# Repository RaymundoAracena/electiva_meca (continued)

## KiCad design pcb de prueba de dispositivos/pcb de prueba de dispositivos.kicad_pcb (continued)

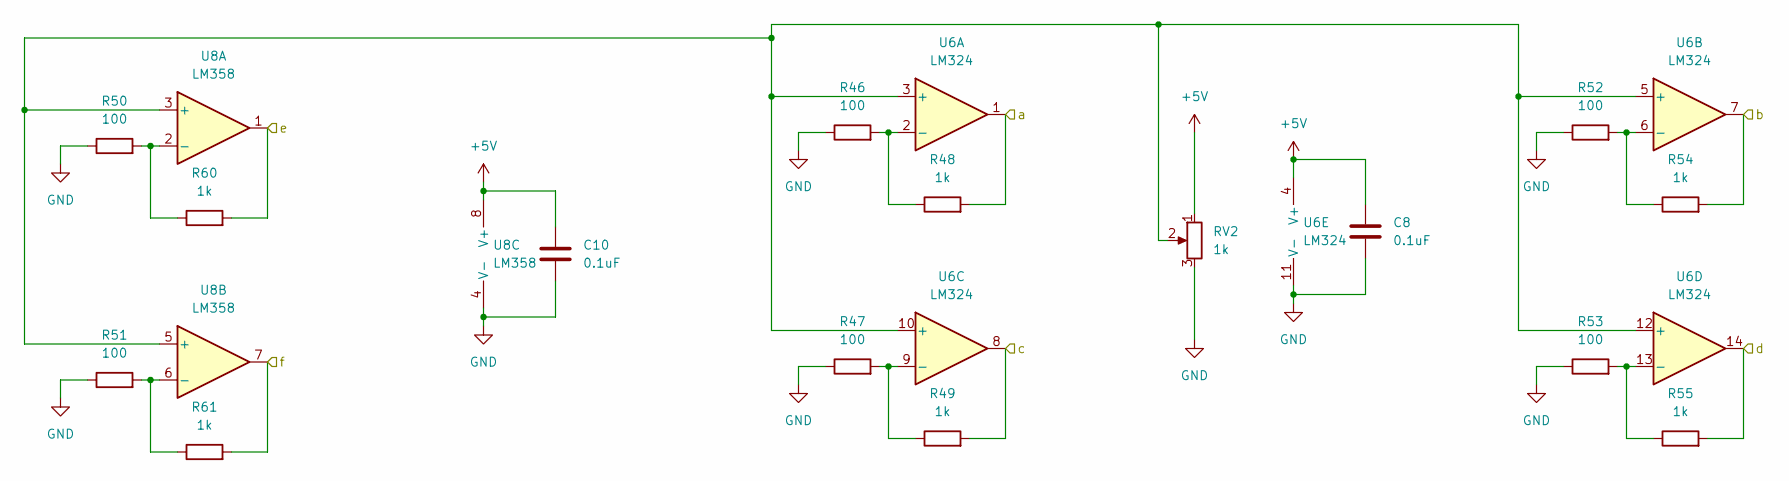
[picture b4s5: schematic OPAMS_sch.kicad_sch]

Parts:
C8, C10: 0.1uF; C_Disc_D5.0mm_W2.5mm_P5.00mm
R46, R47, R50, R51, R52, R53: 100; R_Axial_DIN0207_L6.3mm_D2.5mm_P10.16mm_Horizontal
R48, R49, R54, R55, R60, R61: 1k; R_Axial_DIN0207_L6.3mm_D2.5mm_P10.16mm_Horizontal
RV2: 1k; TerminalBlock_bornier-3_P5.08mm
U6: LM324; DIP-14_W7.62mm_LongPads
U8: LM358; DIP-8_W7.62mm_LongPads

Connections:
+5V: C8.2, C10.2, RV2.1, U6.4 (V+), U8.8 (V+); also elsewhere on the board
/OPAMS Y REGULADO/a: R48.2, U6.1; also elsewhere on the board
/OPAMS Y REGULADO/b: R54.2, U6.7; also elsewhere on the board
/OPAMS Y REGULADO/c: R49.2, U6.8; also elsewhere on the board
/OPAMS Y REGULADO/d: R55.2, U6.14; also elsewhere on the board
/OPAMS Y REGULADO/e: R60.2, U8.1; also elsewhere on the board
/OPAMS Y REGULADO/f: R61.2, U8.7; also elsewhere on the board
GND: C8.1, C10.1, R46.1, R47.1, R50.1, R51.1, R52.1, R53.1, RV2.3, U6.11 (V-), U8.4 (V-); also elsewhere on the board
unnamed: R46.2, R48.1, U6.2 (-)
unnamed: R47.2, R49.1, U6.9 (-)
unnamed: R50.2, R60.1, U8.2 (-)
unnamed: R51.2, R61.1, U8.6 (-)
unnamed: R52.2, R54.1, U6.6 (-)
unnamed: R53.2, R55.1, U6.13 (-)
unnamed: RV2.2, U6.3 (+), U6.5 (+), U6.10 (+), U6.12 (+), U8.3 (+), U8.5 (+)

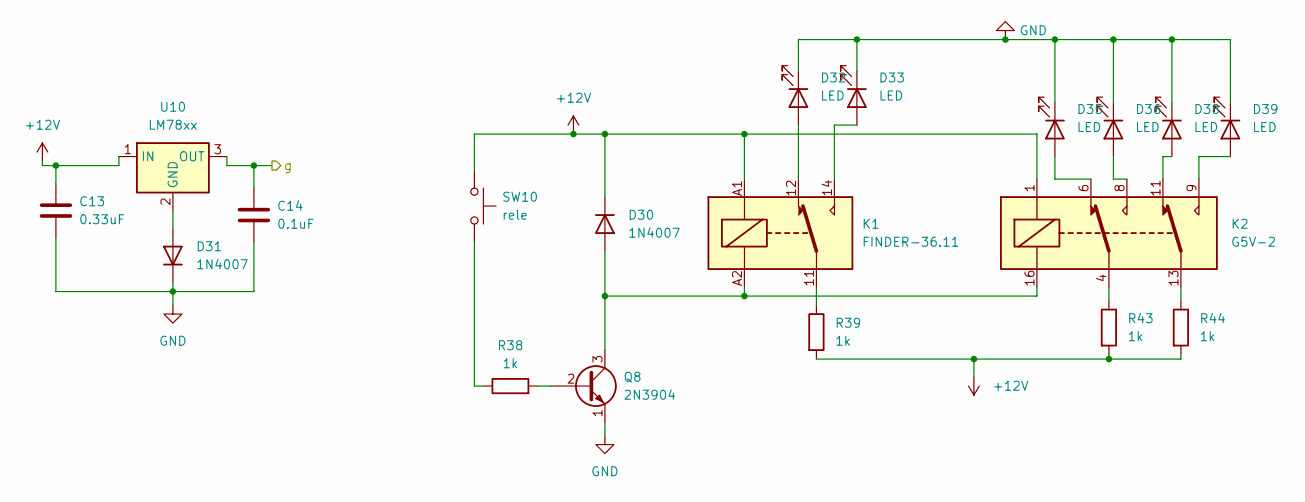
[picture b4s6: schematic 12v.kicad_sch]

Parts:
C13: 0.33uF; C_Disc_D5.0mm_W2.5mm_P5.00mm
C14: 0.1uF; C_Disc_D5.0mm_W2.5mm_P5.00mm
D30, D31: 1N4007; D_DO-41_SOD81_P10.16mm_Horizontal
D32, D33, D35, D36, D38, D39: LED; LED_D5.0mm
K1: FINDER-36.11; Relay_SPDT_Finder_36.11
K2: G5V-2; Relay_DPDT_Omron_G5V-2
Q8: 2N3904; TO-92_Wide
R38, R39, R43, R44: 1k; R_Axial_DIN0207_L6.3mm_D2.5mm_P10.16mm_Horizontal
SW10: rele; SW_PUSH_6mm
U10: LM78xx; TO-220-3_Vertical

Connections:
+12V: C13.1, D30.1 (K), K1.A1, K2.1, R39.2, R43.2, R44.2, SW10.1, U10.1 (IN); also elsewhere on the board
/12v/g: C14.1, U10.3 (OUT); also elsewhere on the board
GND: C13.2, C14.2, D31.1 (K), D32.1 (K), D33.1 (K), D35.1 (K), D36.1 (K), D38.1 (K), D39.1 (K), Q8.1 (E); also elsewhere on the board
unnamed: D30.2 (A), K1.A2, K2.16, Q8.3 (C)
unnamed: D31.2 (A), U10.2 (GND)
unnamed: D32.2 (A), K1.12
unnamed: D33.2 (A), K1.14
unnamed: D35.2 (A), K2.6
unnamed: D36.2 (A), K2.8
unnamed: D38.2 (A), K2.11
unnamed: D39.2 (A), K2.9
unnamed: K1.11, R39.1
unnamed: K2.4, R43.1
unnamed: K2.13, R44.1
unnamed: Q8.2 (B), R38.2
unnamed: R38.1, SW10.2

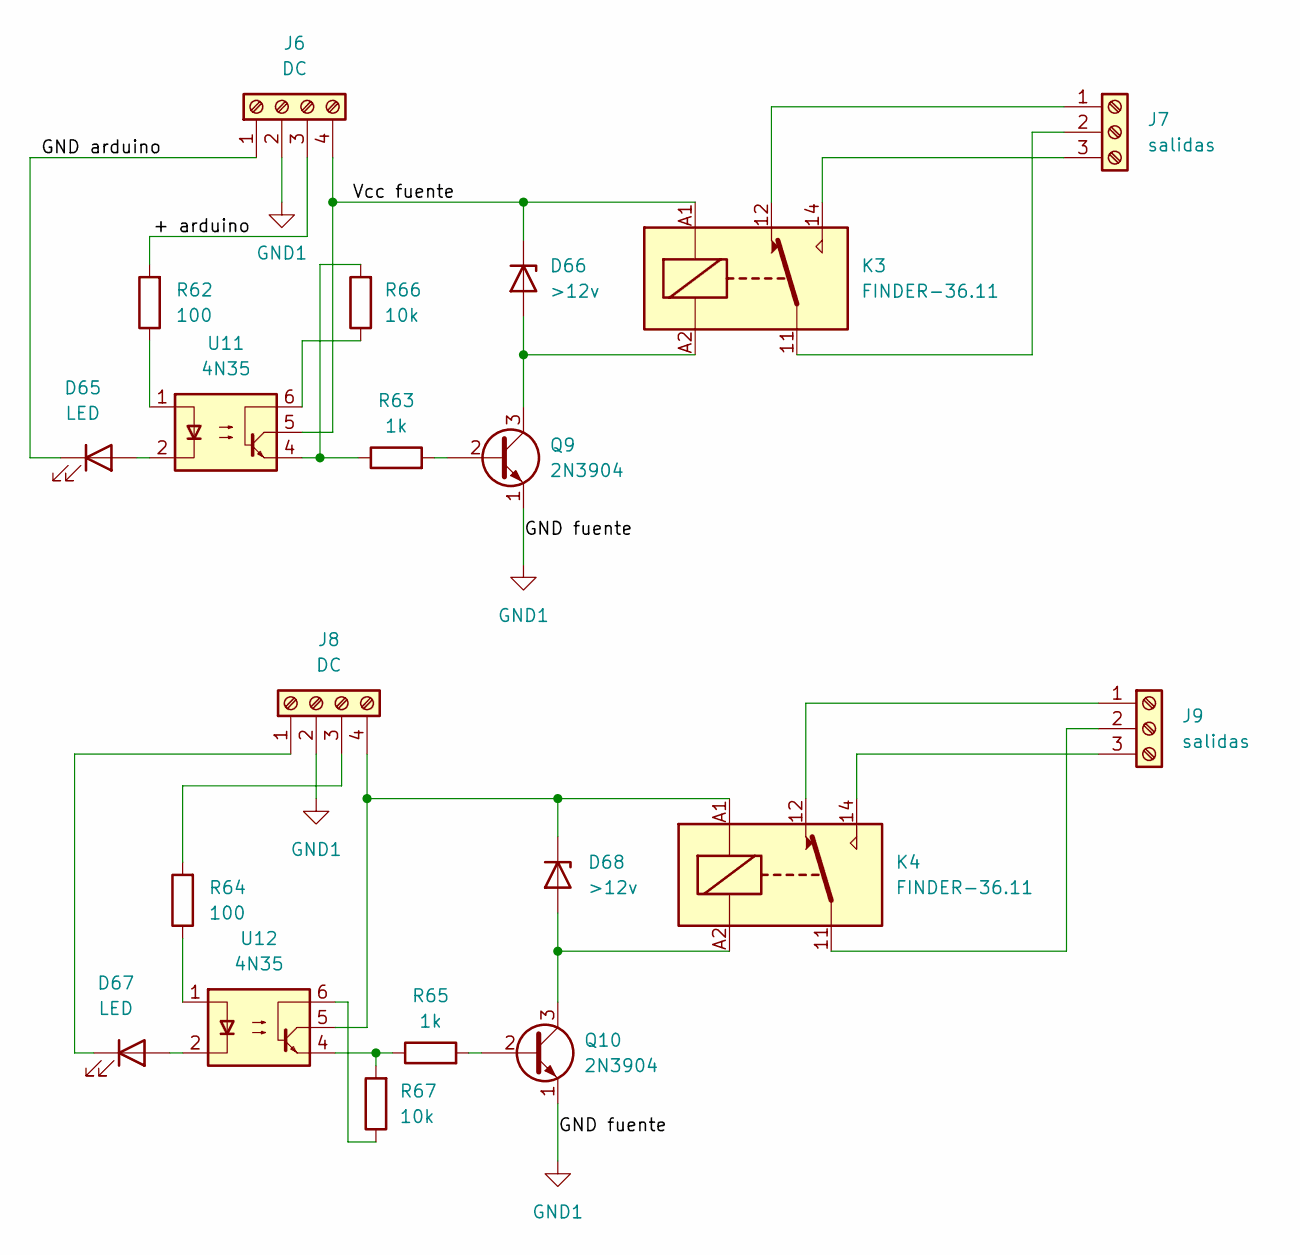
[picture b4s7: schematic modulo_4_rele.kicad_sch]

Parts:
D65, D67: LED; LED_D5.0mm
D66, D68: >12v; D_A-405_P10.16mm_Horizontal
J6, J8: DC; PinHeader_1x04_P2.54mm_Vertical
J7, J9: salidas; TerminalBlock_bornier-3_P5.08mm
K3, K4: FINDER-36.11; Relay_SPDT_Finder_36.11
Q9, Q10: 2N3904; TO-92_Wide
R62, R64: 100; R_Axial_DIN0207_L6.3mm_D2.5mm_P10.16mm_Horizontal
R63, R65: 1k; R_Axial_DIN0207_L6.3mm_D2.5mm_P10.16mm_Horizontal
R66, R67: 10k; R_Axial_DIN0207_L6.3mm_D2.5mm_P10.16mm_Horizontal
U11, U12: 4N35; DIP-6_W7.62mm

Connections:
/modulo_4_rele/+ arduino: J6.3, R62.2
/modulo_4_rele/GND arduino: D65.1 (K), J6.1
/modulo_4_rele/Vcc fuente: D66.1 (K), J6.4, K3.A1, U11.5
GND1: J6.2, J8.2, Q9.1 (E), Q10.1 (E)
unnamed: D65.2 (A), U11.2
unnamed: D66.2 (A), K3.A2, Q9.3 (C)
unnamed: D67.1 (K), J8.1
unnamed: D67.2 (A), U12.2
unnamed: D68.1 (K), J8.4, K4.A1, U12.5
unnamed: D68.2 (A), K4.A2, Q10.3 (C)
unnamed: J7.1, K3.12
unnamed: J7.2, K3.11
unnamed: J7.3, K3.14
unnamed: J8.3, R64.2
unnamed: J9.1, K4.12
unnamed: J9.2, K4.11
unnamed: J9.3, K4.14
unnamed: Q9.2 (B), R63.2
unnamed: Q10.2 (B), R65.2
unnamed: R62.1, U11.1
unnamed: R63.1, R66.2, U11.4
unnamed: R64.1, U12.1
unnamed: R65.1, R67.2, U12.4
unnamed: R66.1, U11.6
unnamed: R67.1, U12.6

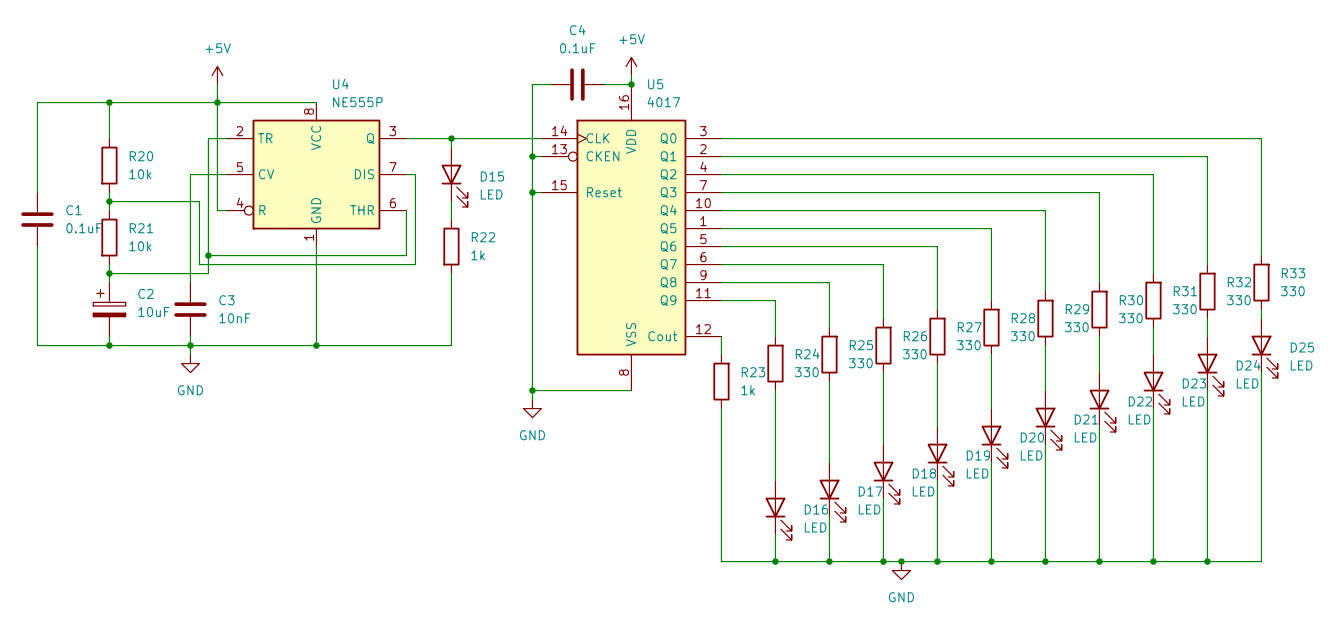
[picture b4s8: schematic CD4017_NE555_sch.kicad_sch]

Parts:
C1, C4: 0.1uF; C_Disc_D5.0mm_W2.5mm_P5.00mm
C2: 10uF; CP_Radial_D5.0mm_P2.50mm
C3: 10nF; C_Disc_D5.0mm_W2.5mm_P5.00mm
D15, D16, D17, D18, D19, D20, D21, D22, D23, D24, D25: LED; LED_D5.0mm
R20, R21: 10k; R_Axial_DIN0207_L6.3mm_D2.5mm_P10.16mm_Horizontal
R22, R23: 1k; R_Axial_DIN0207_L6.3mm_D2.5mm_P10.16mm_Horizontal
R24, R25, R26, R27, R28, R29, R30, R31, R32, R33: 330; R_Axial_DIN0207_L6.3mm_D2.5mm_P10.16mm_Horizontal
U4: NE555P; DIP-8_W7.62mm
U5: 4017; DIP-16_W7.62mm_LongPads

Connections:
+5V: C1.2, C4.1, R20.1, U4.4 (R), U4.8 (VCC), U5.16 (VDD); also elsewhere on the board
GND: C1.1, C2.2, C3.2, C4.2, D16.1 (K), D17.1 (K), D18.1 (K), D19.1 (K), D20.1 (K), D21.1 (K), D22.1 (K), D23.1 (K), D24.1 (K), D25.1 (K), R22.2, R23.1, U4.1 (GND), U5.8 (VSS), U5.13 (CKEN), U5.15 (Reset); also elsewhere on the board
unnamed: C2.1, R21.2, U4.2 (TR), U4.6 (THR)
unnamed: C3.1, U4.5 (CV)
unnamed: D15.1 (K), R22.1
unnamed: D15.2 (A), U4.3 (Q), U5.14 (CLK)
unnamed: D16.2 (A), R24.1
unnamed: D17.2 (A), R25.1
unnamed: D18.2 (A), R26.1
unnamed: D19.2 (A), R27.1
unnamed: D20.2 (A), R28.1
unnamed: D21.2 (A), R29.1
unnamed: D22.2 (A), R30.1
unnamed: D23.2 (A), R31.1
unnamed: D24.2 (A), R32.1
unnamed: D25.2 (A), R33.1
unnamed: R20.2, R21.1, U4.7 (DIS)
unnamed: R23.2, U5.12 (Cout)
unnamed: R24.2, U5.11 (Q9)
unnamed: R25.2, U5.9 (Q8)
unnamed: R26.2, U5.6 (Q7)
unnamed: R27.2, U5.5 (Q6)
unnamed: R28.2, U5.1 (Q5)
unnamed: R29.2, U5.10 (Q4)
unnamed: R30.2, U5.7 (Q3)
unnamed: R31.2, U5.4 (Q2)
unnamed: R32.2, U5.2 (Q1)
unnamed: R33.2, U5.3 (Q0)

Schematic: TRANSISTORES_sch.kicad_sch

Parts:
D26, D28, D34, D37: LED; LED_D5.0mm
D27: SCR; TO-225
Q1: 2N3904; TO-92_Wide
Q2: BD137; TO-126-3_Vertical
Q3: TIP122; TO-220-3_Vertical
Q4: 2N3906; TO-92_Wide
Q5: BD136; TO-126-3_Vertical
Q6: TIP125; TO-220-3_Vertical
R34, R35, R40, R41: 1k; R_Axial_DIN0207_L6.3mm_D2.5mm_P10.16mm_Horizontal
R36, R37, R42, R45: 330; R_Axial_DIN0207_L6.3mm_D2.5mm_P10.16mm_Horizontal
R56: 10k; R_Axial_DIN0207_L6.3mm_D2.5mm_P10.16mm_Horizontal
SW6: ON; SW_PUSH_6mm
SW7, SW9: sw; SW_PUSH_6mm
SW8: OFF; SW_PUSH_6mm

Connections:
+5V: D26.2 (A), D28.2 (A), D34.2 (A), D37.2 (A), SW6.2, SW7.2, SW9.2; also elsewhere on the board
GND: D27.3 (K), Q1.1 (E), Q2.1 (E), Q3.3 (E), Q4.3 (C), Q5.2 (C), Q6.2 (C), R40.1, R45.1, R56.1, SW8.2; also elsewhere on the board
unnamed: D26.1 (K), R36.2
unnamed: D27.1 (G), R35.2, R56.2
unnamed: D27.2 (A), R36.1, SW8.1
unnamed: D28.1 (K), R37.2
unnamed: D34.1 (K), R42.2
unnamed: D37.1 (K), R45.2
unnamed: Q1.2 (B), Q2.3 (B), Q3.1 (B), R34.2
unnamed: Q1.3 (C), Q2.2 (C), Q3.2 (C), R37.1
unnamed: Q4.1 (E), Q5.1 (E), Q6.3 (E), R42.1
unnamed: Q4.2 (B), Q5.3 (B), Q6.1 (B), R41.2
unnamed: R34.1, SW7.1
unnamed: R35.1, SW6.1
unnamed: R40.2, R41.1, SW9.1

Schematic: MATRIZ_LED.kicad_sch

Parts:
D40, D41, D42, D43, D44, D45, D46, D47, D48, D49, D50, D51, D52, D53, D54, D55, D56, D57, D58, D59, D60, D61, D62, D63, D64: LED; LED_D5.0mm
J3: + matriz led; PinSocket_1x05_P2.54mm_Vertical
J4: GND matriz; PinSocket_1x05_P2.54mm_Vertical

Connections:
unnamed: D40.1 (K), D45.1 (K), D50.1 (K), D55.1 (K), D60.1 (K), J4.1
unnamed: D40.2 (A), D41.2 (A), D42.2 (A), D43.2 (A), D44.2 (A), J3.1
unnamed: D41.1 (K), D46.1 (K), D51.1 (K), D56.1 (K), D61.1 (K), J4.2
unnamed: D42.1 (K), D47.1 (K), D52.1 (K), D57.1 (K), D62.1 (K), J4.3
unnamed: D43.1 (K), D48.1 (K), D53.1 (K), D58.1 (K), D63.1 (K), J4.4
unnamed: D44.1 (K), D49.1 (K), D54.1 (K), D59.1 (K), D64.1 (K), J4.5
unnamed: D45.2 (A), D46.2 (A), D47.2 (A), D48.2 (A), D49.2 (A), J3.2
unnamed: D50.2 (A), D51.2 (A), D52.2 (A), D53.2 (A), D54.2 (A), J3.3
unnamed: D55.2 (A), D56.2 (A), D57.2 (A), D58.2 (A), D59.2 (A), J3.4
unnamed: D60.2 (A), D61.2 (A), D62.2 (A), D63.2 (A), D64.2 (A), J3.5

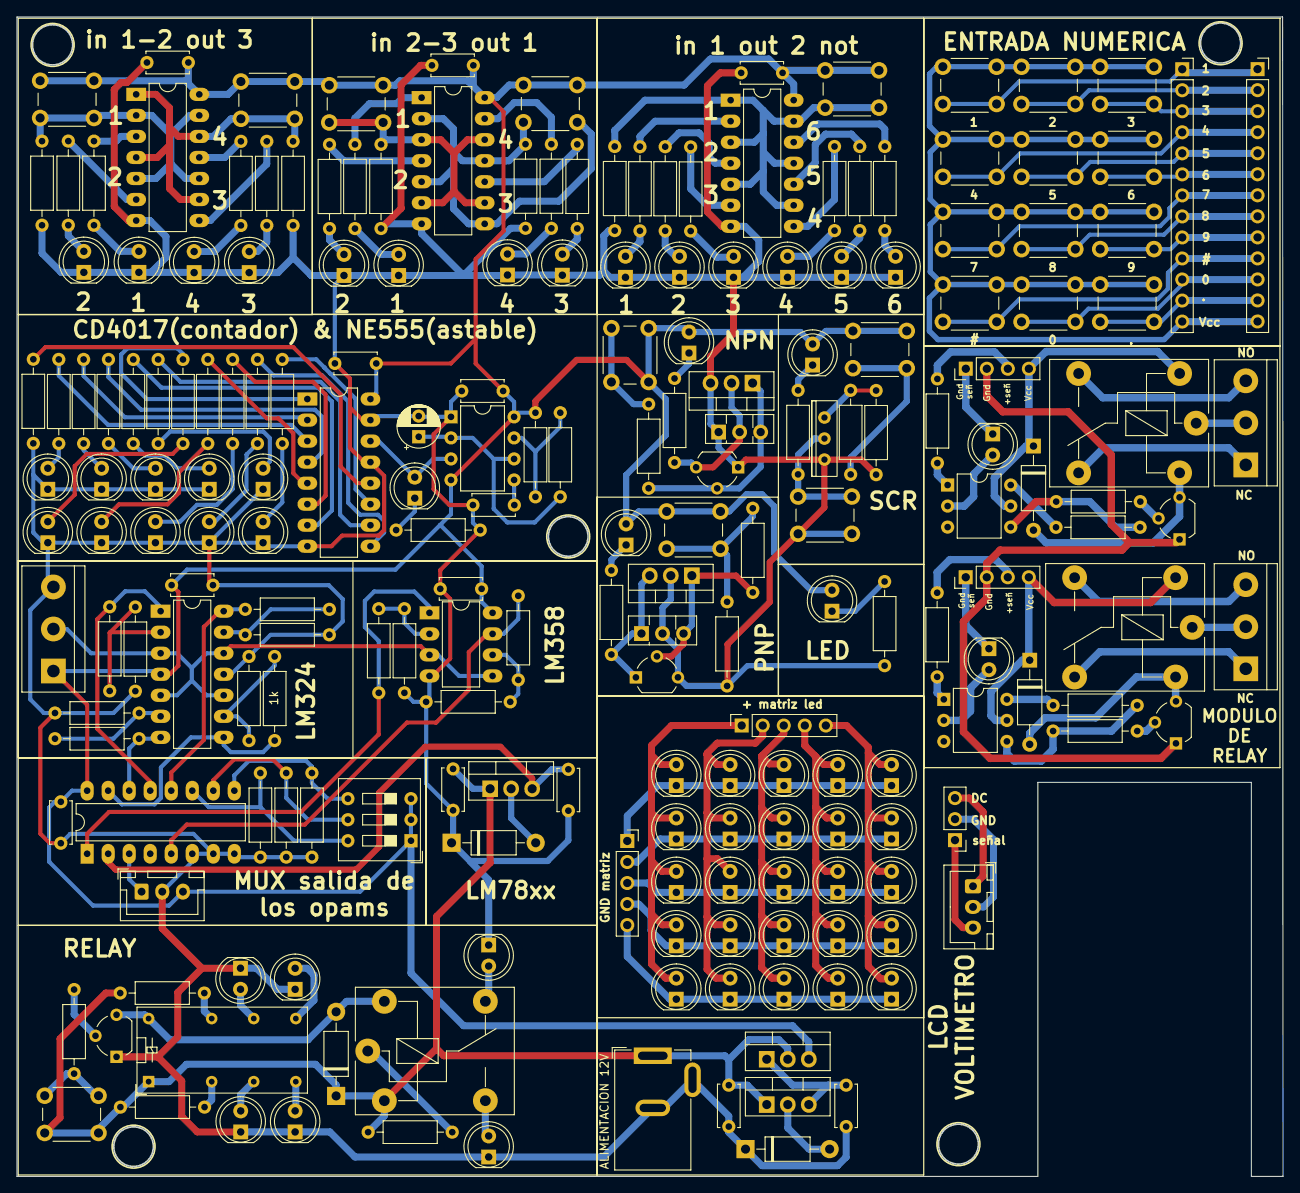
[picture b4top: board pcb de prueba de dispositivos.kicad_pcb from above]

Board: 2 copper layers, 152.9 x 140.1 mm, 211 parts (0 on the bottom side), 159 nets.

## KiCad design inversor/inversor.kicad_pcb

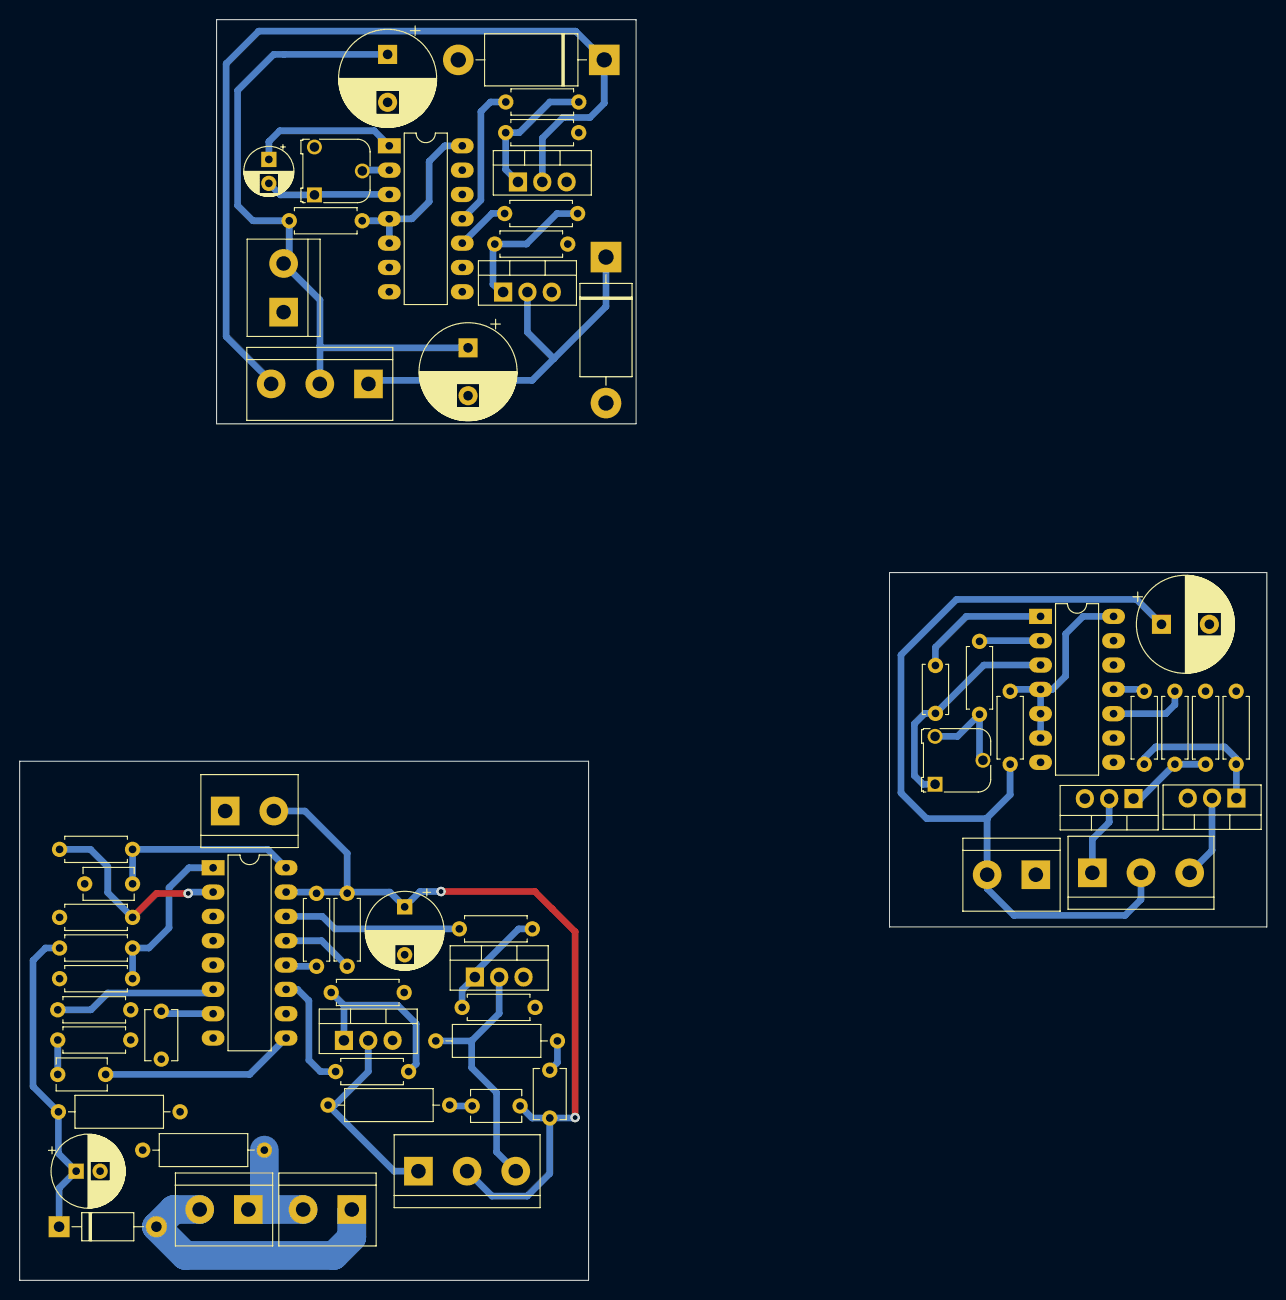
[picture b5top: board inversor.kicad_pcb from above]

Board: 2 copper layers, 130.2 x 131.6 mm, 61 parts (0 on the bottom side), 47 nets.

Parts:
C1: 10nF; C_Disc_D5.0mm_W2.5mm_P5.00mm
C2, C10, C12: 1000uF; CP_Radial_D10.0mm_P5.00mm
C3: 100uF; CP_Radial_D8.0mm_P5.00mm
C4, C5: 0.1uF; C_Disc_D5.1mm_W3.2mm_P5.00mm
C6: 0.001uF; C_Disc_D5.1mm_W3.2mm_P5.00mm
C7, C8: 100nF; C_Disc_D5.1mm_W3.2mm_P5.00mm
C9: 1uF; CP_Radial_D7.5mm_P2.50mm
C11: 4.7uF; CP_Radial_D5.0mm_P2.50mm
D1: 1N4007; D_DO-41_SOD81_P10.16mm_Horizontal
D2, D3: 1N5408; D_DO-201AD_P15.24mm_Horizontal
J1: Screw_Terminal_01x03; TerminalBlock_bornier-3_P5.08mm
J2, J6, J7: DC; TerminalBlock_bornier-2_P5.08mm
J3: 12-12; TerminalBlock_bornier-3_P5.08mm
J4: 120; TerminalBlock_bornier-2_P5.08mm
J5: 120ref; TerminalBlock_bornier-2_P5.08mm
J8: AC; TerminalBlock_bornier-3_P5.08mm
Q1, Q2, Q3, Q4, Q5, Q6: IRF3205; TO-220-3_Vertical
R1, R15: 330; R_Axial_DIN0207_L6.3mm_D2.5mm_P7.62mm_Horizontal
R2: 390k; R_Axial_DIN0207_L6.3mm_D2.5mm_P7.62mm_Horizontal
R3, R4: 220; R_Axial_DIN0207_L6.3mm_D2.5mm_P7.62mm_Horizontal
R5, R6, R16, R22: 2200; R_Axial_DIN0207_L6.3mm_D2.5mm_P7.62mm_Horizontal
R7, R8, R19, R21: 1k; R_Axial_DIN0207_L6.3mm_D2.5mm_P7.62mm_Horizontal
R9, R13: 100k; R_Axial_DIN0207_L6.3mm_D2.5mm_P7.62mm_Horizontal
R10, R11: 47k; R_Axial_DIN0207_L6.3mm_D2.5mm_P7.62mm_Horizontal
R12, R27, R28: 10k; R_Axial_DIN0207_L6.3mm_D2.5mm_P7.62mm_Horizontal
R14: 20k; R_Axial_DIN0207_L6.3mm_D2.5mm_P7.62mm_Horizontal
R18, R20: 22; R_Axial_DIN0207_L6.3mm_D2.5mm_P7.62mm_Horizontal
R23: 56/2W; R_Axial_DIN0309_L9.0mm_D3.2mm_P12.70mm_Horizontal
R24: 66/2W; R_Axial_DIN0309_L9.0mm_D3.2mm_P12.70mm_Horizontal
R25: 200k/2W; R_Axial_DIN0309_L9.0mm_D3.2mm_P12.70mm_Horizontal
R26: 1k/1W; R_Axial_DIN0309_L9.0mm_D3.2mm_P12.70mm_Horizontal
RV1, RV2: 100k; Potentiometer_Runtron_RM-065_Vertical
U1, U3: 4047; DIP-14_W7.62mm_LongPads
U2: SG3525; DIP-16_W7.62mm_LongPads

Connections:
+12P: C10.1, C12.1, J7.2, J8.2, R15.1
+12V: C3.1, C7.1, C8.2, J3.2, J6.2, R7.1, R8.2, U2.15 (VIN)
+12VA: C2.1, J1.2, J2.2, R1.1
GND: C3.2, C4.1, C5.1, C9.2, J6.1, Q3.3 (S), Q6.3 (S), R9.1, R11.1, R12.1, R14.1, R16.2, R22.2, R25.1, R26.2, U2.4 (OSC), U2.5 (CT), U2.8 (SS)
GND1: C2.2, J2.1, Q1.3 (S), Q2.3 (S), R5.1, R6.1, U1.7 (VSS), U1.8 (+TRIGGER), U1.9 (EXT_RESET), U1.12 (RETRIGGER)
GNDA: C10.2, C12.2, D2.2 (A), D3.2 (A), J7.1, Q4.3 (S), Q5.3 (S), R27.1, R28.1, U3.6 (-TRIGGER), U3.7 (VSS), U3.8 (+TRIGGER), U3.9 (EXT_RESET), U3.12 (RETRIGGER)
unnamed: C6.1, R14.2
unnamed: C7.2, R23.2
unnamed: C8.1, R24.1
unnamed: D1.2 (A), J4.2, J5.1
unnamed: D2.1 (K), J8.1, Q4.2 (D)
unnamed: D3.1 (K), J8.3, Q5.2 (D)
unnamed: J1.1, Q1.2 (D)
unnamed: J1.3, Q2.2 (D)
unnamed: J3.1, Q3.2 (D), R23.1
unnamed: J3.3, Q6.2 (D), R24.2
unnamed: J4.1, J5.2, R25.2
unnamed: Q1.1 (G), R3.2, R5.2
unnamed: Q2.1 (G), R4.2, R6.2
unnamed: Q3.1 (G), R16.1, R18.2
unnamed: Q4.1 (G), R19.2, R27.2
unnamed: Q5.1 (G), R21.2, R28.2
unnamed: Q6.1 (G), R20.2, R22.1
unnamed: R2.1, RV1.2, RV1.3
unnamed: R1.2, U1.4 (~ASTABLE), U1.5 (ASTABLE), U1.6 (-TRIGGER), U1.14 (VDD)
unnamed: C1.2, U1.1 (C)
unnamed: R3.1, U1.10 (Q)
unnamed: R2.2, U1.2 (R)
unnamed: C1.1, RV1.1, U1.3 (RC_COMMON)
unnamed: R4.1, U1.11 (~Q)
unnamed: C6.2, U2.9 (COMP)
unnamed: C4.2, U2.7 (DISCH)
unnamed: R8.1, U2.12 (GND)
unnamed: R12.2, R13.1, U2.1 (INV)
unnamed: R10.2, R11.2, U2.2 (NI)
unnamed: R18.1, U2.11 (OUTA)
unnamed: R20.1, U2.14 (OUTB)
unnamed: C5.2, R10.1, U2.16 (REF)
unnamed: R9.2, U2.6 (RT)
unnamed: R7.2, U2.13 (VC)
unnamed: R15.2, U3.4 (~ASTABLE), U3.5 (ASTABLE), U3.14 (VDD)
unnamed: C11.1, U3.1 (C)
unnamed: R19.1, U3.10 (Q)
unnamed: RV2.2, U3.2 (R)
unnamed: C11.2, RV2.1, U3.3 (RC_COMMON)
unnamed: R21.1, U3.11 (~Q)
pb1: C9.1, D1.1 (K), R13.2, R26.1

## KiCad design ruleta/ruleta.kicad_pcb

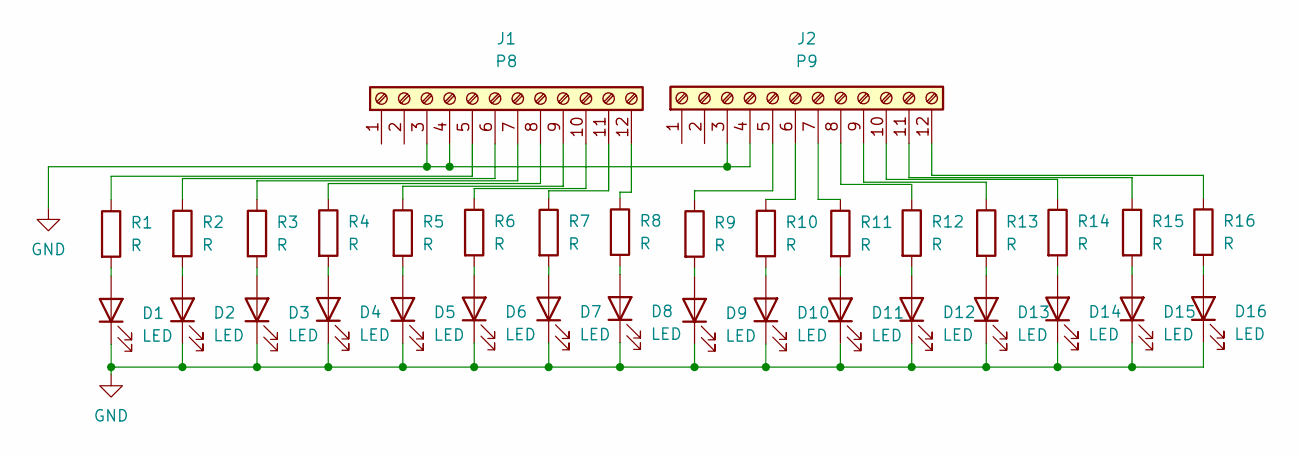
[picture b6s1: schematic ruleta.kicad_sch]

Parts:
D1, D2, D3, D4, D5, D6, D7, D8, D9, D10, D11, D12, D13, D14, D15, D16: LED; LED_D5.0mm
J1: P8; PinHeader_2x06_P2.54mm_Horizontal
J2: P9; PinHeader_2x06_P2.54mm_Horizontal
R1, R2, R3, R4, R5, R6, R7, R8, R9, R10, R11, R12, R13, R14, R15, R16: R; R_Axial_DIN0207_L6.3mm_D2.5mm_P10.16mm_Horizontal

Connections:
GND: D1.1 (K), D2.1 (K), D3.1 (K), D4.1 (K), D5.1 (K), D6.1 (K), D7.1 (K), D8.1 (K), D9.1 (K), D10.1 (K), D11.1 (K), D12.1 (K), D13.1 (K), D14.1 (K), D15.1 (K), D16.1 (K), J1.3, J1.4, J2.3, J2.4
unnamed: D1.2 (A), R1.2
unnamed: D2.2 (A), R2.2
unnamed: D3.2 (A), R3.2
unnamed: D4.2 (A), R4.2
unnamed: D5.2 (A), R5.2
unnamed: D6.2 (A), R6.2
unnamed: D7.2 (A), R7.2
unnamed: D8.2 (A), R8.2
unnamed: D9.2 (A), R9.2
unnamed: D10.2 (A), R10.2
unnamed: D11.2 (A), R11.2
unnamed: D12.2 (A), R12.2
unnamed: D13.2 (A), R13.2
unnamed: D14.2 (A), R14.2
unnamed: D15.2 (A), R15.2
unnamed: D16.2 (A), R16.2
unnamed: J1.5, R1.1
unnamed: J1.6, R2.1
unnamed: J1.7, R3.1
unnamed: J1.8, R4.1
unnamed: J1.9, R5.1
unnamed: J1.10, R6.1
unnamed: J1.11, R7.1
unnamed: J1.12, R8.1
unnamed: J2.5, R9.1
unnamed: J2.6, R10.1
unnamed: J2.7, R11.1
unnamed: J2.8, R12.1
unnamed: J2.9, R13.1
unnamed: J2.10, R14.1
unnamed: J2.11, R15.1
unnamed: J2.12, R16.1

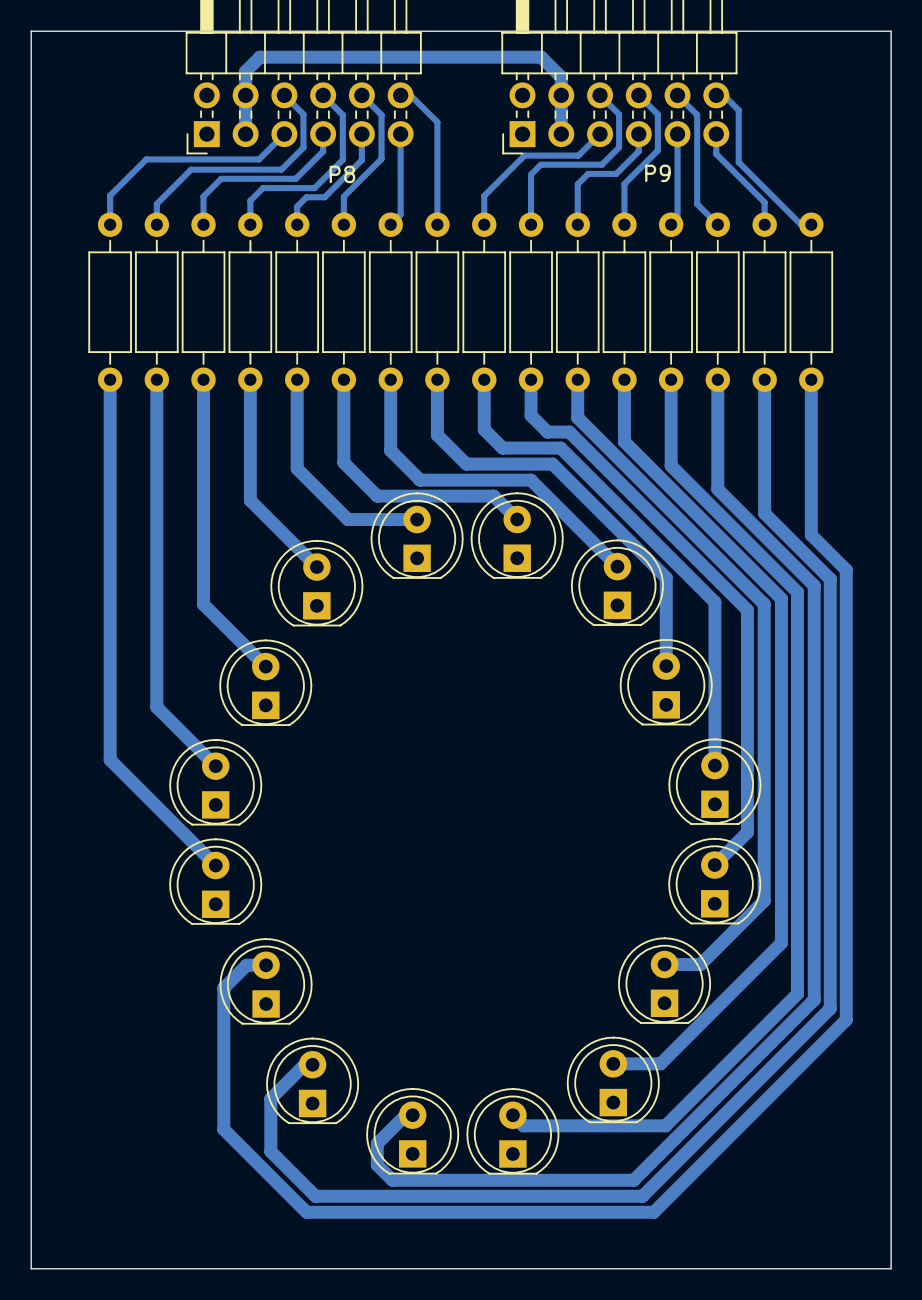
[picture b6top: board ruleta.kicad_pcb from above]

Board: 2 copper layers, 56.4 x 81.1 mm, 34 parts (0 on the bottom side), 33 nets.

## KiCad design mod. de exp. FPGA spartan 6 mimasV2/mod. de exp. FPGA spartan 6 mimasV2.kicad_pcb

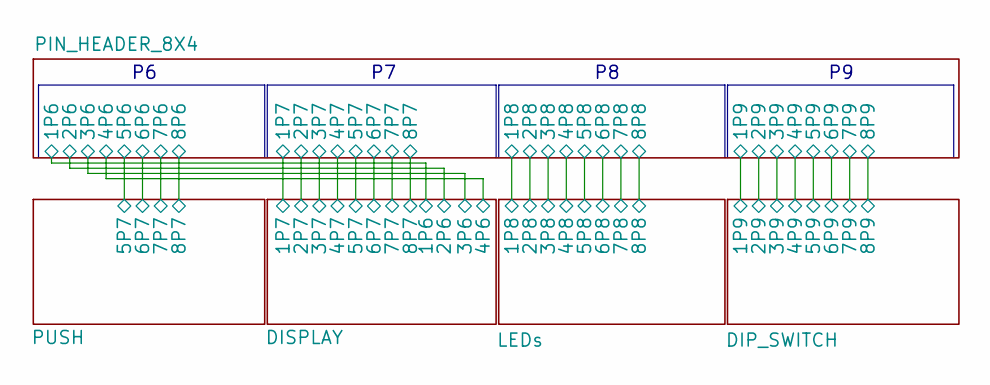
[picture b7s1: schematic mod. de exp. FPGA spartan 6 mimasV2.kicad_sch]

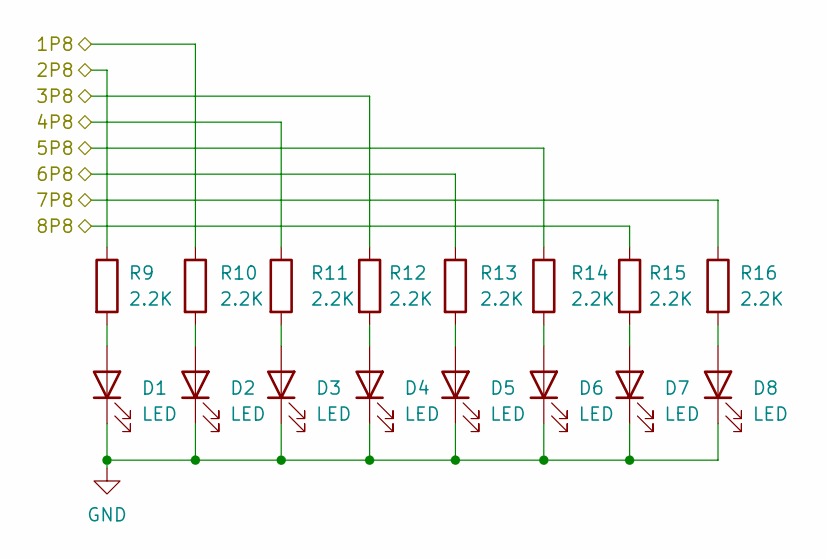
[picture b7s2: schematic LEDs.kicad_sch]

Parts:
D1, D2, D3, D4, D5, D6, D7, D8: LED; LED_0805_2012Metric
R9, R10, R11, R12, R13, R14, R15, R16: 2.2K; R_0805_2012Metric

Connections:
/LEDs/1P8: R10.1; also elsewhere on the board
/LEDs/2P8: R9.1; also elsewhere on the board
/LEDs/3P8: R12.1; also elsewhere on the board
/LEDs/4P8: R11.1; also elsewhere on the board
/LEDs/5P8: R14.1; also elsewhere on the board
/LEDs/6P8: R13.1; also elsewhere on the board
/LEDs/7P8: R16.1; also elsewhere on the board
/LEDs/8P8: R15.1; also elsewhere on the board
GND: D1.1 (K), D2.1 (K), D3.1 (K), D4.1 (K), D5.1 (K), D6.1 (K), D7.1 (K), D8.1 (K); also elsewhere on the board
unnamed: D1.2 (A), R9.2
unnamed: D2.2 (A), R10.2
unnamed: D3.2 (A), R11.2
unnamed: D4.2 (A), R12.2
unnamed: D5.2 (A), R13.2
unnamed: D6.2 (A), R14.2
unnamed: D7.2 (A), R15.2
unnamed: D8.2 (A), R16.2

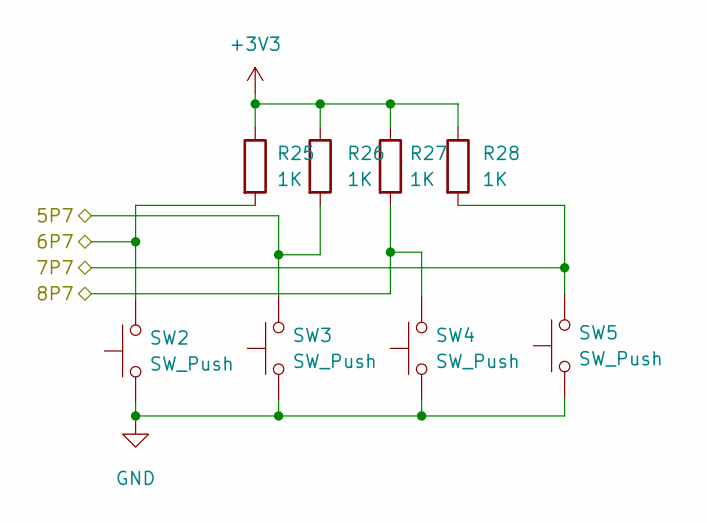
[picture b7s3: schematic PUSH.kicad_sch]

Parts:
R25, R26, R27, R28: 1K; R_0805_2012Metric
SW2, SW3, SW4, SW5: SW_Push; SW_PUSH_6mm

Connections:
+3V3: R25.1, R26.1, R27.1, R28.1; also elsewhere on the board
/PIN_HEADER_8X4/5P6: R26.2, SW3.2; also elsewhere on the board
/PIN_HEADER_8X4/6P6: R25.2, SW2.2; also elsewhere on the board
/PIN_HEADER_8X4/7P6: R28.2, SW5.2; also elsewhere on the board
/PIN_HEADER_8X4/8P6: R27.2, SW4.2; also elsewhere on the board
GND: SW2.1, SW3.1, SW4.1, SW5.1; also elsewhere on the board

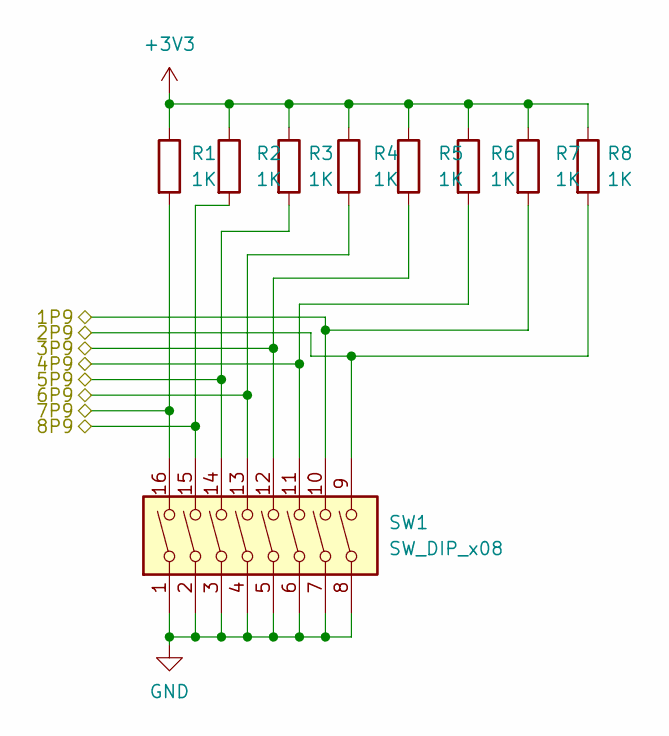
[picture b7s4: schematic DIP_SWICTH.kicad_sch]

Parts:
R1, R2, R3, R4, R5, R6, R7, R8: 1K; R_0805_2012Metric
SW1: SW_DIP_x08; SW_DIP_SPSTx08_Slide_6.7x21.88mm_W7.62mm_P2.54mm_LowProfile

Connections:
+3V3: R1.1, R2.1, R3.1, R4.1, R5.1, R6.1, R7.1, R8.1; also elsewhere on the board
/DIP_SWITCH/1P9: R7.2, SW1.10; also elsewhere on the board
/DIP_SWITCH/2P9: R8.2, SW1.9; also elsewhere on the board
/DIP_SWITCH/3P9: R5.2, SW1.12; also elsewhere on the board
/DIP_SWITCH/4P9: R6.2, SW1.11; also elsewhere on the board
/DIP_SWITCH/5P9: R3.2, SW1.14; also elsewhere on the board
/DIP_SWITCH/6P9: R4.2, SW1.13; also elsewhere on the board
/DIP_SWITCH/7P9: R1.2, SW1.16; also elsewhere on the board
/DIP_SWITCH/8P9: R2.2, SW1.15; also elsewhere on the board
GND: SW1.1, SW1.2, SW1.3, SW1.4, SW1.5, SW1.6, SW1.7, SW1.8; also elsewhere on the board

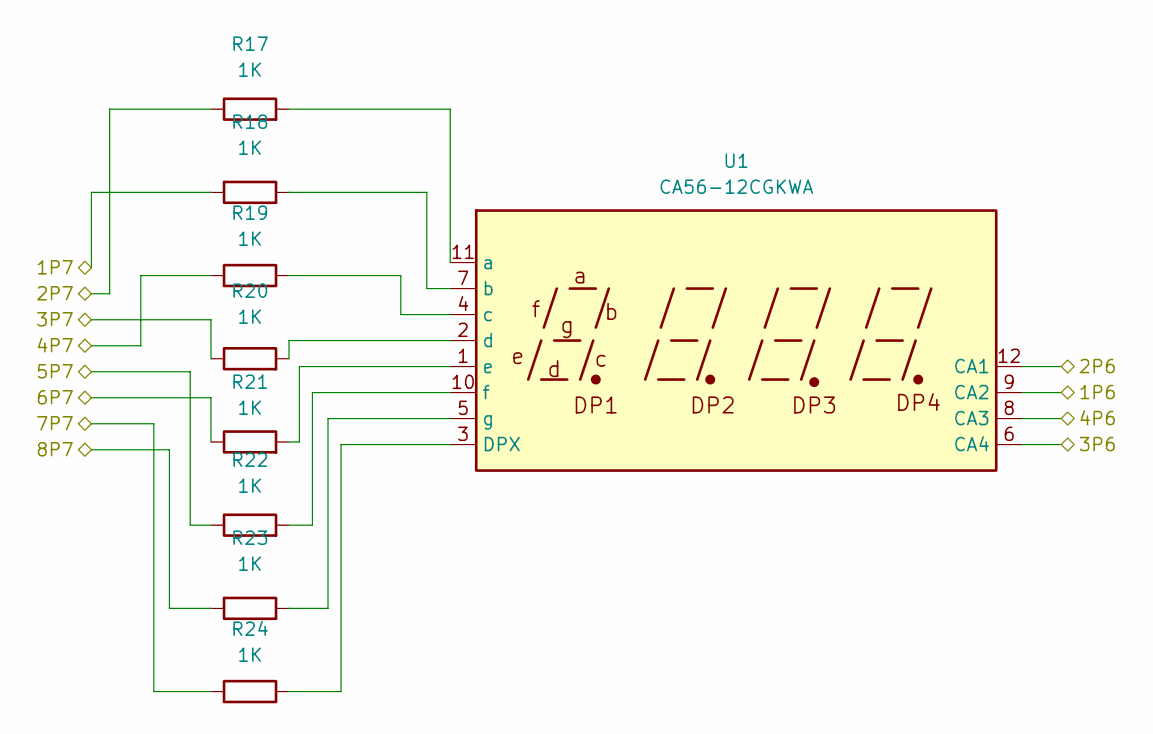
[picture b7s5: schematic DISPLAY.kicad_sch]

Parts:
R17, R18, R19, R20, R21, R22, R23, R24: 1K; R_0805_2012Metric
U1: CA56-12CGKWA

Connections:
/DISPLAY/1P6: U1.9 (CA2); also elsewhere on the board
/DISPLAY/1P7: R18.1; also elsewhere on the board
/DISPLAY/2P6: U1.12 (CA1); also elsewhere on the board
/DISPLAY/2P7: R17.1; also elsewhere on the board
/DISPLAY/3P6: U1.6 (CA4); also elsewhere on the board
/DISPLAY/3P7: R20.1; also elsewhere on the board
/DISPLAY/4P6: U1.8 (CA3); also elsewhere on the board
/DISPLAY/4P7: R19.1; also elsewhere on the board
/DISPLAY/5P7: R22.1; also elsewhere on the board
/DISPLAY/6P7: R21.1; also elsewhere on the board
/DISPLAY/7P7: R24.1; also elsewhere on the board
/DISPLAY/8P7: R23.1; also elsewhere on the board
unnamed: R17.2, U1.11 (a)
unnamed: R18.2, U1.7 (b)
unnamed: R19.2, U1.4 (c)
unnamed: R20.2, U1.2 (d)
unnamed: R21.2, U1.1 (e)
unnamed: R22.2, U1.10 (f)
unnamed: R23.2, U1.5 (g)
unnamed: R24.2, U1.3 (DPX)

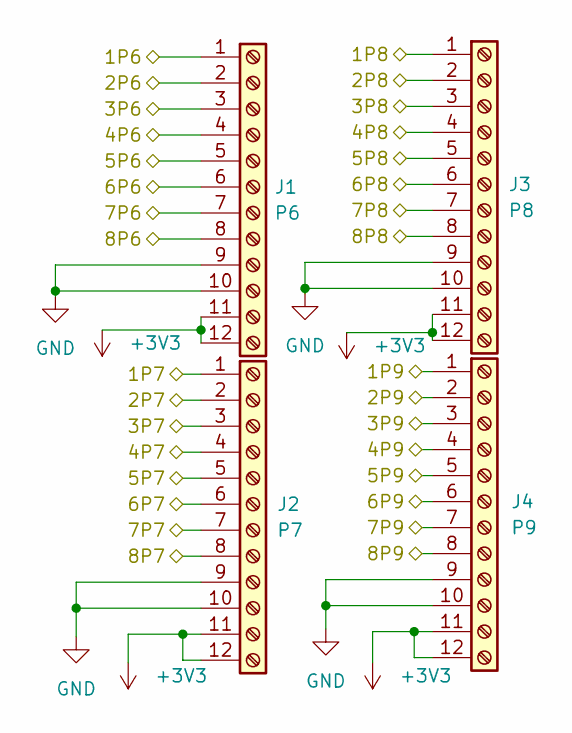
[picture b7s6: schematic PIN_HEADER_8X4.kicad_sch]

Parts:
J1: P6; PinHeader_2x06_P2.54mm_Vertical
J2: P7; PinHeader_2x06_P2.54mm_Vertical
J3: P8; PinHeader_2x06_P2.54mm_Vertical
J4: P9; PinHeader_2x06_P2.54mm_Vertical

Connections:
+3V3: J1.11, J1.12, J2.11, J2.12, J3.11, J3.12, J4.11, J4.12; also elsewhere on the board
/DIP_SWITCH/1P9: J4.1; also elsewhere on the board
/DIP_SWITCH/2P9: J4.2; also elsewhere on the board
/DIP_SWITCH/3P9: J4.3; also elsewhere on the board
/DIP_SWITCH/4P9: J4.4; also elsewhere on the board
/DIP_SWITCH/5P9: J4.5; also elsewhere on the board
/DIP_SWITCH/6P9: J4.6; also elsewhere on the board
/DIP_SWITCH/7P9: J4.7; also elsewhere on the board
/DIP_SWITCH/8P9: J4.8; also elsewhere on the board
/DISPLAY/1P6: J1.1; also elsewhere on the board
/DISPLAY/1P7: J2.1; also elsewhere on the board
/DISPLAY/2P6: J1.2; also elsewhere on the board
/DISPLAY/2P7: J2.2; also elsewhere on the board
/DISPLAY/3P6: J1.3; also elsewhere on the board
/DISPLAY/3P7: J2.3; also elsewhere on the board
/DISPLAY/4P6: J1.4; also elsewhere on the board
/DISPLAY/4P7: J2.4; also elsewhere on the board
/DISPLAY/5P7: J2.5; also elsewhere on the board
/DISPLAY/6P7: J2.6; also elsewhere on the board
/DISPLAY/7P7: J2.7; also elsewhere on the board
/DISPLAY/8P7: J2.8; also elsewhere on the board
/LEDs/1P8: J3.1; also elsewhere on the board
/LEDs/2P8: J3.2; also elsewhere on the board
/LEDs/3P8: J3.3; also elsewhere on the board
/LEDs/4P8: J3.4; also elsewhere on the board
/LEDs/5P8: J3.5; also elsewhere on the board
/LEDs/6P8: J3.6; also elsewhere on the board
/LEDs/7P8: J3.7; also elsewhere on the board
/LEDs/8P8: J3.8; also elsewhere on the board
/PIN_HEADER_8X4/5P6: J1.5; also elsewhere on the board
/PIN_HEADER_8X4/6P6: J1.6; also elsewhere on the board
/PIN_HEADER_8X4/7P6: J1.7; also elsewhere on the board
/PIN_HEADER_8X4/8P6: J1.8; also elsewhere on the board
GND: J1.9, J1.10, J2.9, J2.10, J3.9, J3.10, J4.9, J4.10; also elsewhere on the board
